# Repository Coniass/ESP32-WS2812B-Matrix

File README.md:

# ESP32 LED Matrix Controller with WLED

This is a project to build a LED matrix controller using an ESP32 microcontroller and the WLED software. The aim is to create a gift prototype that can drive an LED matrix and possibly a small screen.

## Overview

The ESP32 microcontroller will be used to drive a 25 WS2812B LED matrix. The WS2812B LEDs will be mounted on the same PCB as the ESP32. A TPD4E02B04 will be used to protect the board from voltage spikes. An AZ1117IH 3.3V voltage regulator will convert the 5V power from the USB C port to 3.3V power for the ESP32. The CH340 USB to serial converter will be used for programming the ESP32 and for USB connectivity.

## Circuit Diagram

The diagram was created using KiCad.

## Programming the ESP32

To program the ESP32, you will need the Arduino IDE and the ESP32 board files installed. Follow the instructions on the [ESP32 Arduino Core GitHub page](https://github.com/espressif/arduino-esp32) to install the board files.

To upload the code to the ESP32, connect it to your computer using a USB cable. In the Arduino IDE, select the appropriate board and serial port, and then upload the code.

## Installing WLED

You can install the WLED software on the ESP32 by following the instructions on the [WLED install page](https://install.wled.me/).

## Contributing

I welcome criticism and suggestions for improvement. If you have any suggestions or improvements, please open an issue or a pull request.

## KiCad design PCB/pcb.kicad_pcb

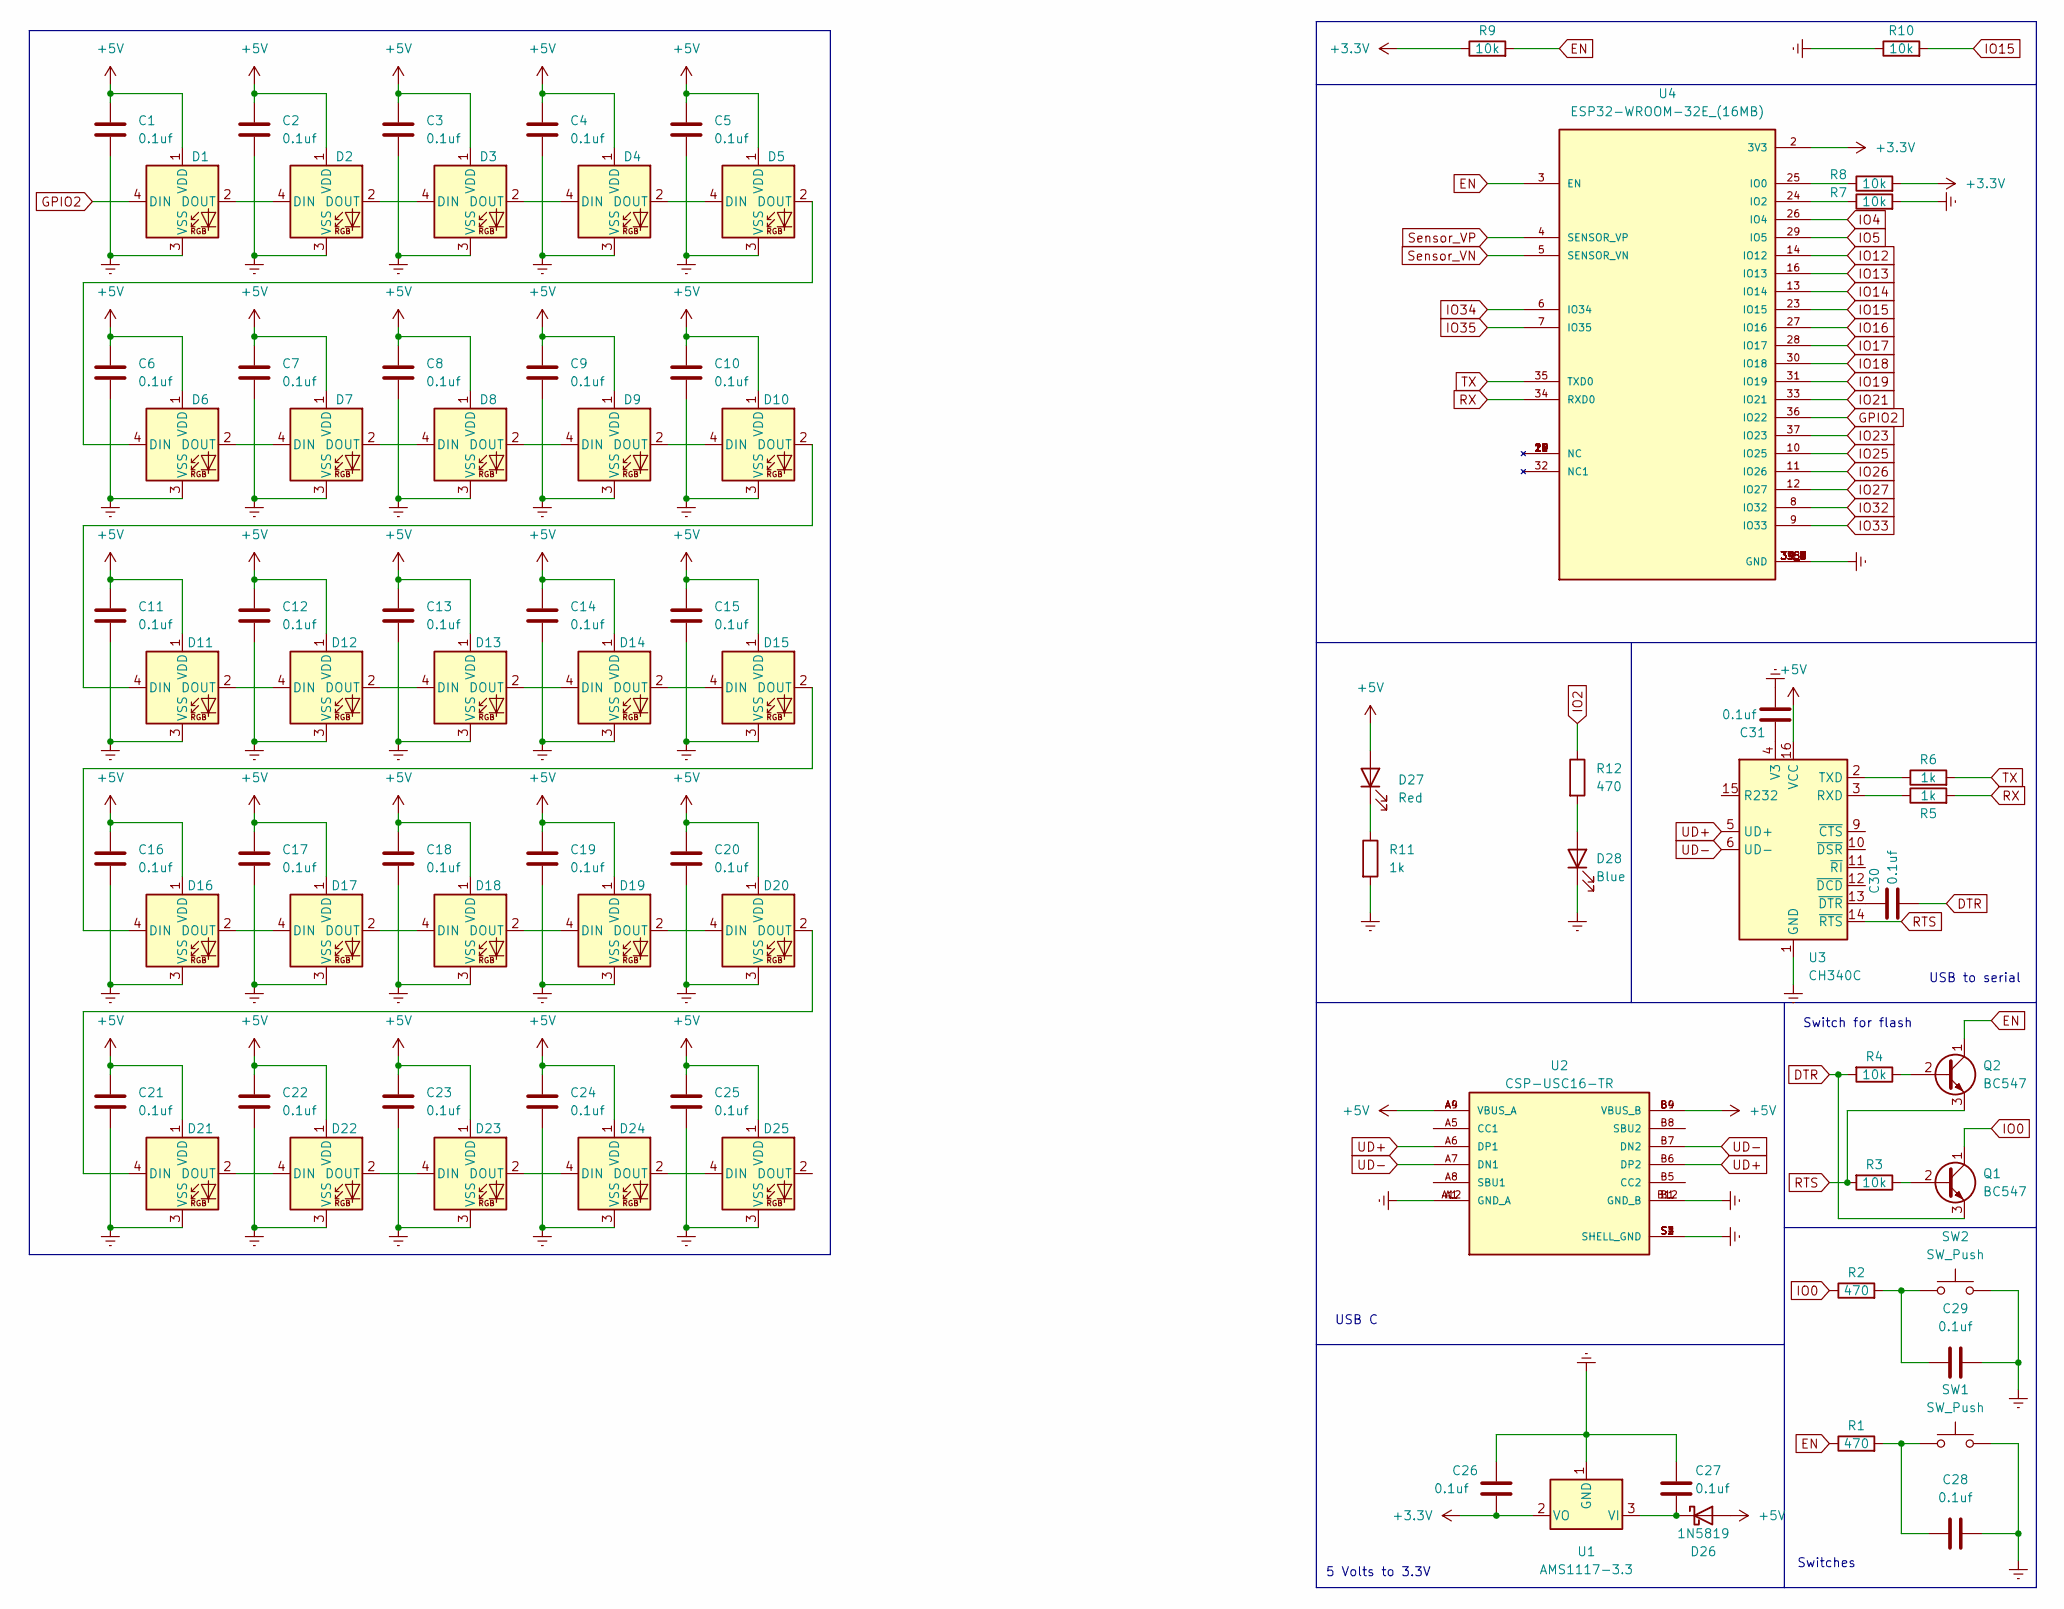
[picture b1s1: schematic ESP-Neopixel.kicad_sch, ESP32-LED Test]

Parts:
C1, C2, C3, C4, C5, C6, C7, C8, C9, C10, C11, C12, C13, C14, C15, C16, C17, C18, C19, C20, C21, C22, C23, C24, C25: 0.1uf; Cap
C26, C27, C28, C29, C30, C31: 0.1uf; C_0805_2012Metric
D1, D2, D3, D4, D5, D6, D7, D8, D9, D10, D11, D12, D13, D14, D15, D16, D17, D18, D19, D20, D21, D22, D23, D24, D25: WS2812B; LED_WS2812B_PLCC4_5.0x5.0mm_P3.2mm
D26: 1N5819; D_SOD-323_HandSoldering
D27: Red; LED_0805_2012Metric
D28: Blue; LED_0805_2012Metric
Q1, Q2: BC547; TSOT-23
R1, R2, R12: 470; R_0805_2012Metric
R3, R4, R7, R8, R9, R10: 10k; R_0805_2012Metric
R5, R6, R11: 1k; R_0805_2012Metric
SW1, SW2: SW_Push; SW_SPST_B3U-1000P
U1: AMS1117-3.3; SOT-223-3_TabPin2
U2: CSP-USC16-TR; VALCON_CSP-USC16-TR; PARTREV A0
U3: CH340C; SOIC-16_3.9x9.9mm_P1.27mm
U4: ESP32-WROOM-32E_(16MB); XCVR_ESP32-WROOM-32E_(16MB); PARTREV 1.4

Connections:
+3.3V: C26.2, R8.2, R9.1, U1.2 (VO), U4.2 (3V3)
+5V: C1.1, C2.1, C3.1, C4.1, C5.1, C6.1, C7.1, C8.1, C9.1, C10.1, C11.1, C12.1, C13.1, C14.1, C15.1, C16.1, C17.1, C18.1, C19.1, C20.1, C21.1, C22.1, C23.1, C24.1, C25.1, D1.1 (VDD), D2.1 (VDD), D3.1 (VDD), D4.1 (VDD), D5.1 (VDD), D6.1 (VDD), D7.1 (VDD), D8.1 (VDD), D9.1 (VDD), D10.1 (VDD), D11.1 (VDD), D12.1 (VDD), D13.1 (VDD), D14.1 (VDD), D15.1 (VDD), D16.1 (VDD), D17.1 (VDD), D18.1 (VDD), D19.1 (VDD), D20.1 (VDD), D21.1 (VDD), D22.1 (VDD), D23.1 (VDD), D24.1 (VDD), D25.1 (VDD), D26.2 (A), D27.2 (A), U2.A4 (VBUS_A), U2.A9 (VBUS_A), U2.B4 (VBUS_B), U2.B9 (VBUS_B), U3.16 (VCC)
DTR: C30.2, Q1.3 (E), R4.2
EN: Q2.1 (C), R1.1, R9.2, U4.3 (EN)
Earth: C1.2, C2.2, C3.2, C4.2, C5.2, C6.2, C7.2, C8.2, C9.2, C10.2, C11.2, C12.2, C13.2, C14.2, C15.2, C16.2, C17.2, C18.2, C19.2, C20.2, C21.2, C22.2, C23.2, C24.2, C25.2, C26.1, C27.1, C28.2, C29.2, C31.2, D1.3 (VSS), D2.3 (VSS), D3.3 (VSS), D4.3 (VSS), D5.3 (VSS), D6.3 (VSS), D7.3 (VSS), D8.3 (VSS), D9.3 (VSS), D10.3 (VSS), D11.3 (VSS), D12.3 (VSS), D13.3 (VSS), D14.3 (VSS), D15.3 (VSS), D16.3 (VSS), D17.3 (VSS), D18.3 (VSS), D19.3 (VSS), D20.3 (VSS), D21.3 (VSS), D22.3 (VSS), D23.3 (VSS), D24.3 (VSS), D25.3 (VSS), D28.1 (K), R7.2, R10.1, R11.2, SW1.2, SW2.2, U1.1 (GND), U2.A1 (GND_A), U2.A12 (GND_A), U2.B1 (GND_B), U2.B12 (GND_B), U2.S1 (SHELL_GND), U2.S2 (SHELL_GND), U2.S3 (SHELL_GND), U2.S4 (SHELL_GND), U3.1 (GND), U4.1 (GND), U4.15 (GND), U4.38 (GND), U4.39_1 (GND), U4.39_2 (GND), U4.39_3 (GND), U4.39_4 (GND), U4.39_5 (GND), U4.39_6 (GND), U4.39_7 (GND), U4.39_8 (GND), U4.39_9 (GND)
GPIO2: D1.4 (DIN), U4.36 (IO22)
IO0: Q1.1 (C), R2.1
IO2: R12.1
IO4: U4.26 (IO4)
IO5: U4.29 (IO5)
IO12: U4.14 (IO12)
IO13: U4.16 (IO13)
IO14: U4.13 (IO14)
IO15: R10.2, U4.23 (IO15)
IO16: U4.27 (IO16)
IO17: U4.28 (IO17)
IO18: U4.30 (IO18)
IO19: U4.31 (IO19)
IO21: U4.33 (IO21)
IO23: U4.37 (IO23)
IO25: U4.10 (IO25)
IO26: U4.11 (IO26)
IO27: U4.12 (IO27)
IO32: U4.8 (IO32)
IO33: U4.9 (IO33)
IO34: U4.6 (IO34)
IO35: U4.7 (IO35)
unnamed: C27.2, D26.1 (K), U1.3 (VI)
unnamed: C28.1, R1.2, SW1.1
unnamed: C29.1, R2.2, SW2.1
unnamed: D1.2 (DOUT), D2.4 (DIN)
unnamed: D2.2 (DOUT), D3.4 (DIN)
unnamed: D3.2 (DOUT), D4.4 (DIN)
unnamed: D4.2 (DOUT), D5.4 (DIN)
unnamed: D5.2 (DOUT), D6.4 (DIN)
unnamed: D6.2 (DOUT), D7.4 (DIN)
unnamed: D7.2 (DOUT), D8.4 (DIN)
unnamed: D8.2 (DOUT), D9.4 (DIN)
unnamed: D10.2 (DOUT), D11.4 (DIN)
unnamed: D9.2 (DOUT), D10.4 (DIN)
unnamed: D11.2 (DOUT), D12.4 (DIN)
unnamed: D12.2 (DOUT), D13.4 (DIN)
unnamed: D13.2 (DOUT), D14.4 (DIN)
unnamed: D14.2 (DOUT), D15.4 (DIN)
unnamed: D15.2 (DOUT), D16.4 (DIN)
unnamed: D16.2 (DOUT), D17.4 (DIN)
unnamed: D17.2 (DOUT), D18.4 (DIN)
unnamed: D18.2 (DOUT), D19.4 (DIN)
unnamed: D19.2 (DOUT), D20.4 (DIN)
unnamed: D20.2 (DOUT), D21.4 (DIN)
unnamed: D21.2 (DOUT), D22.4 (DIN)
unnamed: D22.2 (DOUT), D23.4 (DIN)
unnamed: D23.2 (DOUT), D24.4 (DIN)
unnamed: D24.2 (DOUT), D25.4 (DIN)
unnamed: D27.1 (K), R11.1
unnamed: D28.2 (A), R12.2
unnamed: Q1.2 (B), R3.1
unnamed: Q2.2 (B), R4.1
unnamed: R6.1, U3.2 (TXD)
unnamed: R5.1, U3.3 (RXD)
unnamed: C31.1, U3.4 (V3)
unnamed: C30.1, U3.13 (~DTR)
unnamed: R7.1, U4.24 (IO2)
unnamed: R8.1, U4.25 (IO0)
RTS: Q2.3 (E), R3.2, U3.14 (~RTS)
RX: R5.2, U4.34 (RXD0)
Sensor_VN: U4.5 (SENSOR_VN)
Sensor_VP: U4.4 (SENSOR_VP)
TX: R6.2, U4.35 (TXD0)
UD+: U2.A6 (DP1), U2.B6 (DP2), U3.5 (UD+)
UD-: U2.A7 (DN1), U2.B7 (DN2), U3.6 (UD-)

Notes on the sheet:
5 Volts to 3.3V
Switch for flash
USB C
USB to serial
Switches

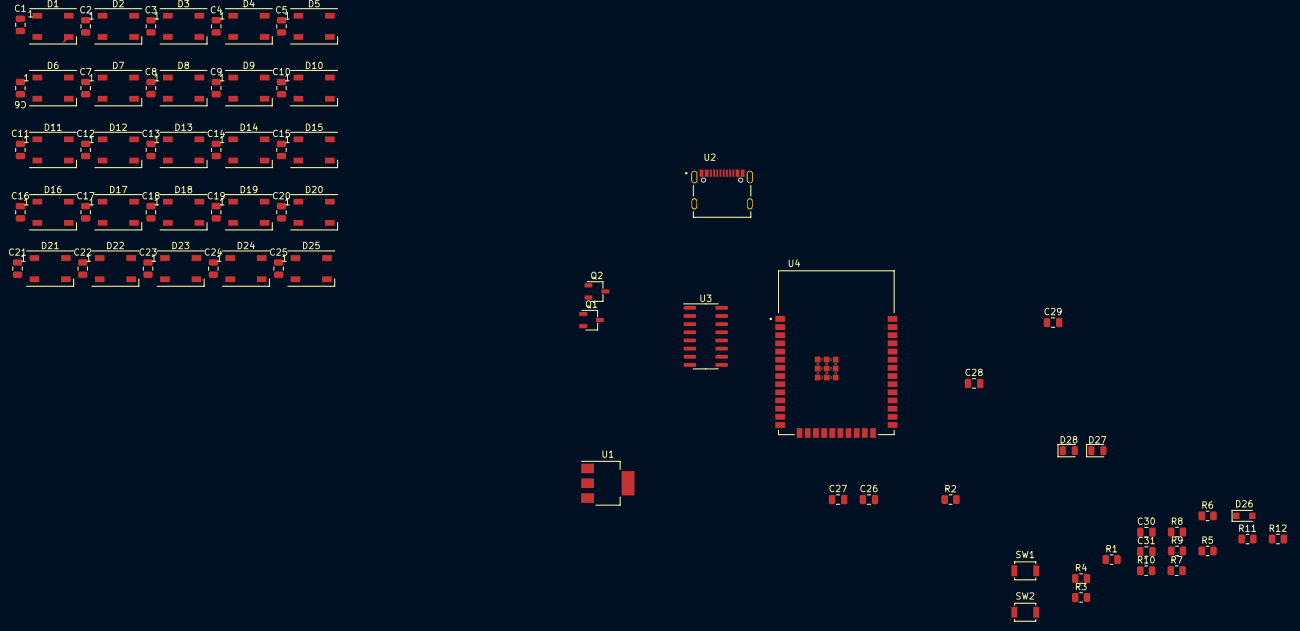
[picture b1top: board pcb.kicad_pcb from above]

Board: 2 copper layers, 79 parts (0 on the bottom side), 50 nets.

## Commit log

2023-01-28 V1 of Schematic
2023-01-28 Changes some crap
2023-01-31 Added 5.1k for PD
2023-03-21 Added high res image
2023-03-21 Updated jpg & pdf
2023-03-22 Fixed some crap (not all of it)
2023-03-23 Added tvs diodes
2023-03-23 Created ReadME
2023-03-24 Changed AMS1117 to AZ1117IH
